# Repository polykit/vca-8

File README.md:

# Polykit VCA-8

This repository contains Kicad schematics and PCB layout for a VCA with 8 independent voices.

# References

http://yusynth.net/Modular/EN/VCA/index.html

https://kassu2000.blogspot.com/2015/10/vca.html

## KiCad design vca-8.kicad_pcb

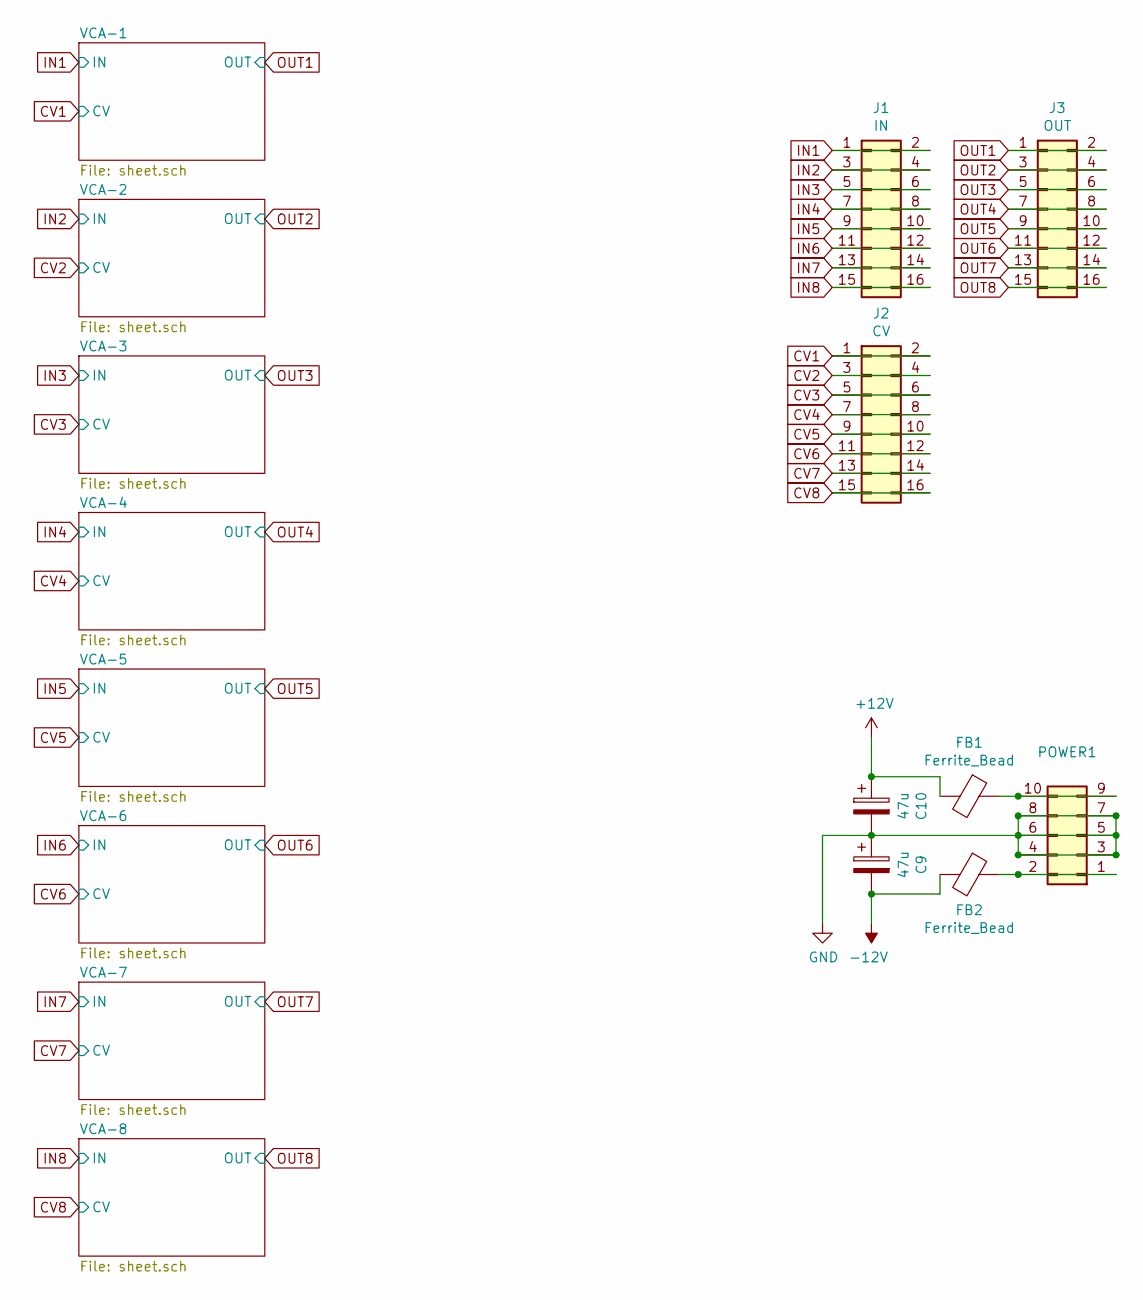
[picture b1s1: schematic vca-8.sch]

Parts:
C9, C10: 47u; CP_Radial_D6.3mm_P2.50mm
FB1, FB2: Ferrite_Bead; R_Axial_DIN0207_L6.3mm_D2.5mm_P10.16mm_Horizontal
J1: IN; IDC-Header_2x08_P2.54mm_Vertical
J2: CV; IDC-Header_2x08_P2.54mm_Vertical
J3: OUT; IDC-Header_2x08_P2.54mm_Vertical
POWER1: Conn_02x05_Odd_Even; IDC-Header_2x05_P2.54mm_Vertical

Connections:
+12V: C10.1, FB1.2; also elsewhere on the board
-12V: C9.2, FB2.2; also elsewhere on the board
CV1: J2.1, J2.2; also elsewhere on the board
CV2: J2.3, J2.4; also elsewhere on the board
CV3: J2.5, J2.6; also elsewhere on the board
CV4: J2.7, J2.8; also elsewhere on the board
CV5: J2.9, J2.10; also elsewhere on the board
CV6: J2.11, J2.12; also elsewhere on the board
CV7: J2.13, J2.14; also elsewhere on the board
CV8: J2.15, J2.16; also elsewhere on the board
GND: C9.1, C10.2, POWER1.3, POWER1.4, POWER1.5, POWER1.6, POWER1.7, POWER1.8; also elsewhere on the board
IN1: J1.1, J1.2; also elsewhere on the board
IN2: J1.3, J1.4; also elsewhere on the board
IN3: J1.5, J1.6; also elsewhere on the board
IN4: J1.7, J1.8; also elsewhere on the board
IN5: J1.9, J1.10; also elsewhere on the board
IN6: J1.11, J1.12; also elsewhere on the board
IN7: J1.13, J1.14; also elsewhere on the board
IN8: J1.15, J1.16; also elsewhere on the board
unnamed: FB1.1, POWER1.9, POWER1.10
unnamed: FB2.1, POWER1.1, POWER1.2
OUT1: J3.1, J3.2; also elsewhere on the board
OUT2: J3.3, J3.4; also elsewhere on the board
OUT3: J3.5, J3.6; also elsewhere on the board
OUT4: J3.7, J3.8; also elsewhere on the board
OUT5: J3.9, J3.10; also elsewhere on the board
OUT6: J3.11, J3.12; also elsewhere on the board
OUT7: J3.13, J3.14; also elsewhere on the board
OUT8: J3.15, J3.16; also elsewhere on the board

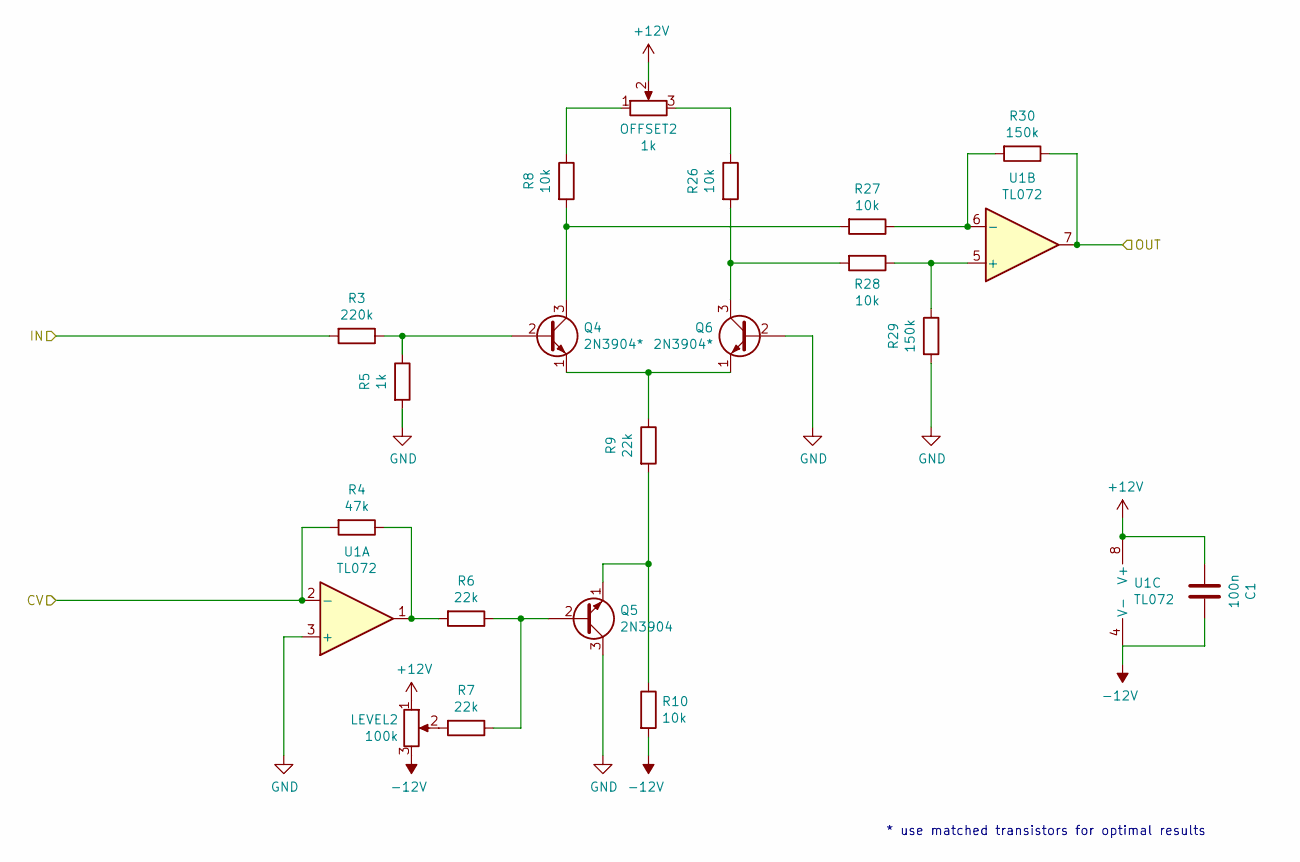
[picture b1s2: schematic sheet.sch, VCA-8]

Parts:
C8: 100n; C_Disc_D5.0mm_W2.5mm_P5.00mm
LEVEL1: 100k; Potentiometer_ACP_CA9-H5_Horizontal
OFFSET1: 1k; Potentiometer_ACP_CA9-H5_Horizontal
Q1, Q2: 2N3904*; TO-92_Inline_Wide
Q3: 2N3904; TO-92_Inline_Wide
R13: 220k; R_Axial_DIN0207_L6.3mm_D2.5mm_P7.62mm_Horizontal
R14: 47k; R_Axial_DIN0207_L6.3mm_D2.5mm_P7.62mm_Horizontal
R15: 1k; R_Axial_DIN0207_L6.3mm_D2.5mm_P7.62mm_Horizontal
R16, R17, R19: 22k; R_Axial_DIN0207_L6.3mm_D2.5mm_P7.62mm_Horizontal
R18, R20, R21, R22, R23: 10k; R_Axial_DIN0207_L6.3mm_D2.5mm_P7.62mm_Horizontal
R24, R25: 150k; R_Axial_DIN0207_L6.3mm_D2.5mm_P7.62mm_Horizontal
U3: TL072; DIP-8_W7.62mm_Socket_LongPads

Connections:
+12V: C8.2, LEVEL1.1, OFFSET1.2, U3.8 (V+); also elsewhere on the board
-12V: C8.1, LEVEL1.3, R20.2, U3.4 (V-); also elsewhere on the board
CV1: R14.2, U3.2 (-); also elsewhere on the board
GND: Q2.2 (B), Q3.3 (C), R15.2, R24.2, U3.3 (+); also elsewhere on the board
IN1: R13.2; also elsewhere on the board
unnamed: LEVEL1.2, R17.2
unnamed: OFFSET1.1, R18.1
unnamed: OFFSET1.3, R21.1
unnamed: Q1.1 (E), Q2.1 (E), R19.1
unnamed: Q1.2 (B), R13.1, R15.1
unnamed: Q1.3 (C), R18.2, R22.2
unnamed: Q2.3 (C), R21.2, R23.2
unnamed: Q3.1 (E), R19.2, R20.1
unnamed: Q3.2 (B), R16.1, R17.1
unnamed: R14.1, R16.2, U3.1
unnamed: R22.1, R25.2, U3.6 (-)
unnamed: R23.1, R24.1, U3.5 (+)
OUT1: R25.1, U3.7; also elsewhere on the board

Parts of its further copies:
C1, C2, C3, C4, C5, C6, C7: 100n; C_Disc_D5.0mm_W2.5mm_P5.00mm
LEVEL2, LEVEL3, LEVEL4, LEVEL5, LEVEL6, LEVEL7, LEVEL8: 100k; Potentiometer_ACP_CA9-H5_Horizontal
OFFSET2, OFFSET3, OFFSET4, OFFSET5, OFFSET6, OFFSET7, OFFSET8: 1k; Potentiometer_ACP_CA9-H5_Horizontal
Q4, Q6, Q7, Q9, Q10, Q12, Q13, Q15, Q16, Q18, Q19, Q21, Q22, Q24: 2N3904*; TO-92_Inline_Wide
Q5, Q8, Q11, Q14, Q17, Q20, Q23: 2N3904; TO-92_Inline_Wide
R3, R33, R48, R63, R78, R93, R108: 220k; R_Axial_DIN0207_L6.3mm_D2.5mm_P7.62mm_Horizontal
R4, R34, R49, R64, R79, R94, R109: 47k; R_Axial_DIN0207_L6.3mm_D2.5mm_P7.62mm_Horizontal
R5, R35, R50, R65, R80, R95, R110: 1k; R_Axial_DIN0207_L6.3mm_D2.5mm_P7.62mm_Horizontal
R6, R7, R9, R36, R37, R39, R51, R52, R54, R66, R67, R69, R81, R82, R84, R96, R97, R99, R111, R112, R114: 22k; R_Axial_DIN0207_L6.3mm_D2.5mm_P7.62mm_Horizontal
R8, R10, R26, R27, R28, R38, R40, R41, R42, R43, R53, R55, R56, R57, R58, R68, R70, R71, R72, R73, R83, R85, R86, R87, R88, R98, R100, R101, R102, R103, R113, R115, R116, R117, R118: 10k; R_Axial_DIN0207_L6.3mm_D2.5mm_P7.62mm_Horizontal
R29, R30, R44, R45, R59, R60, R74, R75, R89, R90, R104, R105, R119, R120: 150k; R_Axial_DIN0207_L6.3mm_D2.5mm_P7.62mm_Horizontal
U1, U2, U4, U5, U6, U7, U8: TL072; DIP-8_W7.62mm_Socket_LongPads

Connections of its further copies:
+12V: C1.2, C2.2, C3.2, C4.2, C5.2, C6.2, C7.2, LEVEL2.1, LEVEL3.1, LEVEL4.1, LEVEL5.1, LEVEL6.1, LEVEL7.1, LEVEL8.1, OFFSET2.2, OFFSET3.2, OFFSET4.2, OFFSET5.2, OFFSET6.2, OFFSET7.2, OFFSET8.2, U1.8 (V+), U2.8 (V+), U4.8 (V+), U5.8 (V+), U6.8 (V+), U7.8 (V+), U8.8 (V+); also elsewhere on the board
-12V: C1.1, C2.1, C3.1, C4.1, C5.1, C6.1, C7.1, LEVEL2.3, LEVEL3.3, LEVEL4.3, LEVEL5.3, LEVEL6.3, LEVEL7.3, LEVEL8.3, R10.2, R40.2, R55.2, R70.2, R85.2, R100.2, R115.2, U1.4 (V-), U2.4 (V-), U4.4 (V-), U5.4 (V-), U6.4 (V-), U7.4 (V-), U8.4 (V-); also elsewhere on the board
CV2: R4.2, U1.2 (-); also elsewhere on the board
CV3: R34.2, U2.2 (-); also elsewhere on the board
CV4: R49.2, U4.2 (-); also elsewhere on the board
CV5: R64.2, U5.2 (-); also elsewhere on the board
CV6: R79.2, U6.2 (-); also elsewhere on the board
CV7: R94.2, U7.2 (-); also elsewhere on the board
CV8: R109.2, U8.2 (-); also elsewhere on the board
GND: Q5.3 (C), Q6.2 (B), Q8.3 (C), Q9.2 (B), Q11.3 (C), Q12.2 (B), Q14.3 (C), Q15.2 (B), Q17.3 (C), Q18.2 (B), Q20.3 (C), Q21.2 (B), Q23.3 (C), Q24.2 (B), R5.2, R29.2, R35.2, R44.2, R50.2, R59.2, R65.2, R74.2, R80.2, R89.2, R95.2, R104.2, R110.2, R119.2, U1.3 (+), U2.3 (+), U4.3 (+), U5.3 (+), U6.3 (+), U7.3 (+), U8.3 (+); also elsewhere on the board
IN2: R3.2; also elsewhere on the board
IN3: R33.2; also elsewhere on the board
IN4: R48.2; also elsewhere on the board
IN5: R63.2; also elsewhere on the board
IN6: R78.2; also elsewhere on the board
IN7: R93.2; also elsewhere on the board
IN8: R108.2; also elsewhere on the board
unnamed: LEVEL2.2, R7.2
unnamed: LEVEL3.2, R37.2
unnamed: LEVEL4.2, R52.2
unnamed: LEVEL5.2, R67.2
unnamed: LEVEL6.2, R82.2
unnamed: LEVEL7.2, R97.2
unnamed: LEVEL8.2, R112.2
unnamed: OFFSET2.1, R8.1
unnamed: OFFSET2.3, R26.1
unnamed: OFFSET3.1, R38.1
unnamed: OFFSET3.3, R41.1
unnamed: OFFSET4.1, R53.1
unnamed: OFFSET4.3, R56.1
unnamed: OFFSET5.1, R68.1
unnamed: OFFSET5.3, R71.1
unnamed: OFFSET6.1, R83.1
unnamed: OFFSET6.3, R86.1
unnamed: OFFSET7.1, R98.1
unnamed: OFFSET7.3, R101.1
unnamed: OFFSET8.1, R113.1
unnamed: OFFSET8.3, R116.1
unnamed: Q4.1 (E), Q6.1 (E), R9.1
unnamed: Q4.2 (B), R3.1, R5.1
unnamed: Q4.3 (C), R8.2, R27.2
unnamed: Q5.1 (E), R9.2, R10.1
unnamed: Q5.2 (B), R6.1, R7.1
unnamed: Q6.3 (C), R26.2, R28.2
unnamed: Q7.1 (E), Q9.1 (E), R39.1
unnamed: Q7.2 (B), R33.1, R35.1
unnamed: Q7.3 (C), R38.2, R42.2
unnamed: Q8.1 (E), R39.2, R40.1
unnamed: Q8.2 (B), R36.1, R37.1
unnamed: Q9.3 (C), R41.2, R43.2
unnamed: Q10.1 (E), Q12.1 (E), R54.1
unnamed: Q10.2 (B), R48.1, R50.1
unnamed: Q10.3 (C), R53.2, R57.2
unnamed: Q11.1 (E), R54.2, R55.1
unnamed: Q11.2 (B), R51.1, R52.1
unnamed: Q12.3 (C), R56.2, R58.2
unnamed: Q13.1 (E), Q15.1 (E), R69.1
unnamed: Q13.2 (B), R63.1, R65.1
unnamed: Q13.3 (C), R68.2, R72.2
unnamed: Q14.1 (E), R69.2, R70.1
unnamed: Q14.2 (B), R66.1, R67.1
unnamed: Q15.3 (C), R71.2, R73.2
unnamed: Q16.1 (E), Q18.1 (E), R84.1
unnamed: Q16.2 (B), R78.1, R80.1
unnamed: Q16.3 (C), R83.2, R87.2
unnamed: Q17.1 (E), R84.2, R85.1
unnamed: Q17.2 (B), R81.1, R82.1
unnamed: Q18.3 (C), R86.2, R88.2
unnamed: Q19.1 (E), Q21.1 (E), R99.1
unnamed: Q19.2 (B), R93.1, R95.1
unnamed: Q19.3 (C), R98.2, R102.2
unnamed: Q20.1 (E), R99.2, R100.1
unnamed: Q20.2 (B), R96.1, R97.1
unnamed: Q21.3 (C), R101.2, R103.2
unnamed: Q22.1 (E), Q24.1 (E), R114.1
unnamed: Q22.2 (B), R108.1, R110.1
unnamed: Q22.3 (C), R113.2, R117.2
unnamed: Q23.1 (E), R114.2, R115.1
unnamed: Q23.2 (B), R111.1, R112.1
unnamed: Q24.3 (C), R116.2, R118.2
unnamed: R4.1, R6.2, U1.1
unnamed: R27.1, R30.2, U1.6 (-)
unnamed: R28.1, R29.1, U1.5 (+)
unnamed: R34.1, R36.2, U2.1
unnamed: R42.1, R45.2, U2.6 (-)
unnamed: R43.1, R44.1, U2.5 (+)
unnamed: R49.1, R51.2, U4.1
unnamed: R57.1, R60.2, U4.6 (-)
unnamed: R58.1, R59.1, U4.5 (+)
unnamed: R64.1, R66.2, U5.1
unnamed: R72.1, R75.2, U5.6 (-)
unnamed: R73.1, R74.1, U5.5 (+)
unnamed: R79.1, R81.2, U6.1
unnamed: R87.1, R90.2, U6.6 (-)
unnamed: R88.1, R89.1, U6.5 (+)
unnamed: R94.1, R96.2, U7.1
unnamed: R102.1, R105.2, U7.6 (-)
unnamed: R103.1, R104.1, U7.5 (+)
unnamed: R109.1, R111.2, U8.1
unnamed: R117.1, R120.2, U8.6 (-)
unnamed: R118.1, R119.1, U8.5 (+)
OUT2: R30.1, U1.7; also elsewhere on the board
OUT3: R45.1, U2.7; also elsewhere on the board
OUT4: R60.1, U4.7; also elsewhere on the board
OUT5: R75.1, U5.7; also elsewhere on the board
OUT6: R90.1, U6.7; also elsewhere on the board
OUT7: R105.1, U7.7; also elsewhere on the board
OUT8: R120.1, U8.7; also elsewhere on the board

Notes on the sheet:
* use matched transistors for optimal results

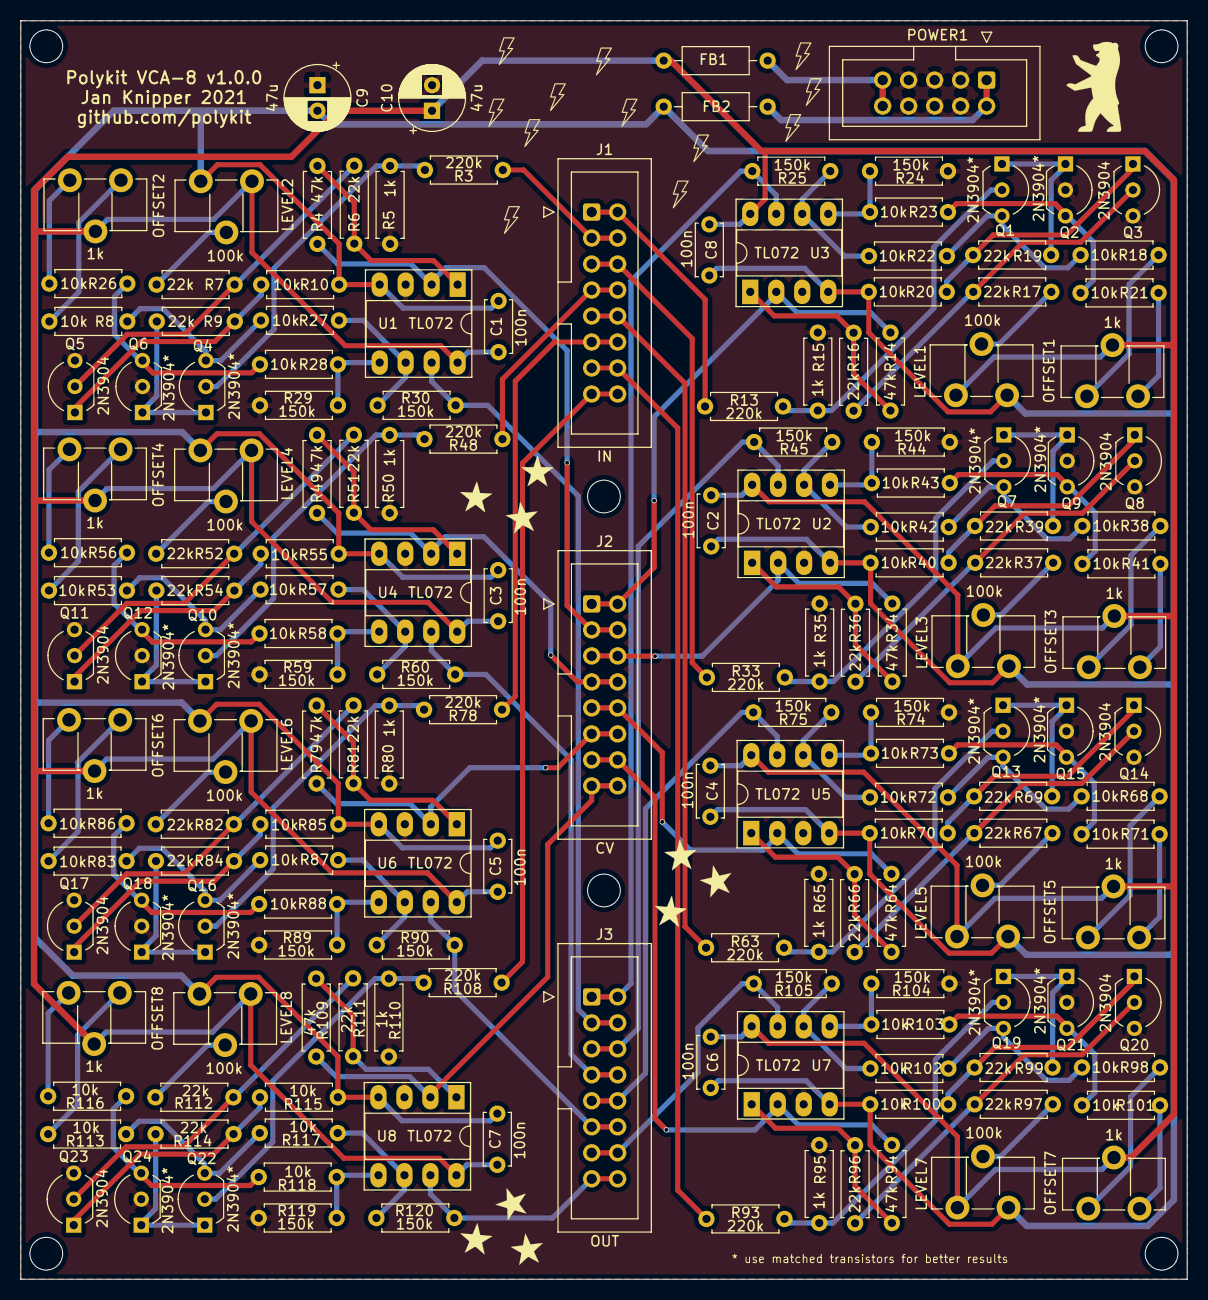
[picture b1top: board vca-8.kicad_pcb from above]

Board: 2 copper layers, 114.0 x 123.0 mm, 168 parts (0 on the bottom side), 125 nets.

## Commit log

2021-06-15 Initial import
